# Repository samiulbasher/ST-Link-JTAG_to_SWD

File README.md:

# ST-Link JTAG to SWD Adapter

A simple, compact adapter that converts a legacy ARM 20-pin JTAG/SWD IDC connector to a standard SWD header. Compatible with ST-Link, J-Link, and other JTAG-based programmers.

---

## 🧰 General

This adapter is designed for developers to **simplify the development and debugging process**.

Instead of dealing with messy jumper wires or complex breakout boards, this provides a clean and reliable solution for converting JTAG to SWD—ideal for use with:

- ST-Link  
- J-Link  
- Other generic JTAG programmers

---

## 📌 Features

- **Plug & Play** — No need to look up datasheets or pinouts  
- **Developer-Friendly** — Saves time and reduces frustration  
- **Labeled Pins** — Clear labeling right on the PCB  
- **Reduces Errors** — Focus on your work, not wiring  
- **Compact** — Just 30x31 mm in size (*2-layer PCB*)

---

## 🧾 Applications

- Debugging and programming ARM Cortex-M microcontrollers  
- Quick SWD access for STM32 and other ARM-based chips  
- Works with any 20-pin JTAG header programmer

---

## 📷 Board Images

> Photos of the adapter and panelized PCB:

---

## 📍 Pin Details

All pin names are printed directly on the PCB.  
Here's a reference for the minimum required connections:

- **4 Pins** (1, 2, 3, 4) — Programming only  
- **6 Pins** (1, 2, 3, 4, 5, 6) — Full debugging + programming

---

## 🔌 Jumper Connection

When using different ST-Link versions:

- **Genuine ST-Link V2 or V3**:  
  Connect `VTarget (VTr)` to `VDD` [target's mcu `VDD`].

- **Clone ST-Link (usually ST-Link V2, e.g., Chinese versions)**:  
  Connect `3V3` to `VDD` [target's mcu `VDD`].

---

## 📦 Specifications

| Attribute           | Value                            |
|---------------------|----------------------------------|
| Dimensions           | 30 mm x 31 mm                   |
| Connector Type       | ARM 20-pin JTAG to SWD Header   |
| Programmer Support   | ST-Link, J-Link, and others     |

---

## ✅ Compatibility

| Programmer       | Compatible |
|------------------|------------|
| ST-Link V2       | ✅         |
| ST-Link V3       | ✅         |
| J-Link           | ✅         |
| Other JTAG headers | ✅       |

---

---

## 📁 Design Files & Gerber Files

- The `JTAG_to_SWD/` directory contains the original **KiCad project files**.  
  If you’d like to modify or customize the board, you can easily do so using KiCad.

- The `gerber/` directory includes **production-ready files** for PCB manufacturing.

  Inside it, you’ll find a `panel/V1.1/` subfolder — this contains the **panelized version** of the PCB (`JTAG_to_SWD_panel_V1.1.zip`).  
  This file is ready to upload directly to [JLCPCB](https://jlcpcb.com) for manufacturing.

💡 This is a **2-layer PCB**, and each panel contains **6 individual boards**.  
That means for just **$2**, you can get **30 PCBs** produced at JLCPCB!

---

## 📝 License

This project is released under the [MIT License](LICENSE).

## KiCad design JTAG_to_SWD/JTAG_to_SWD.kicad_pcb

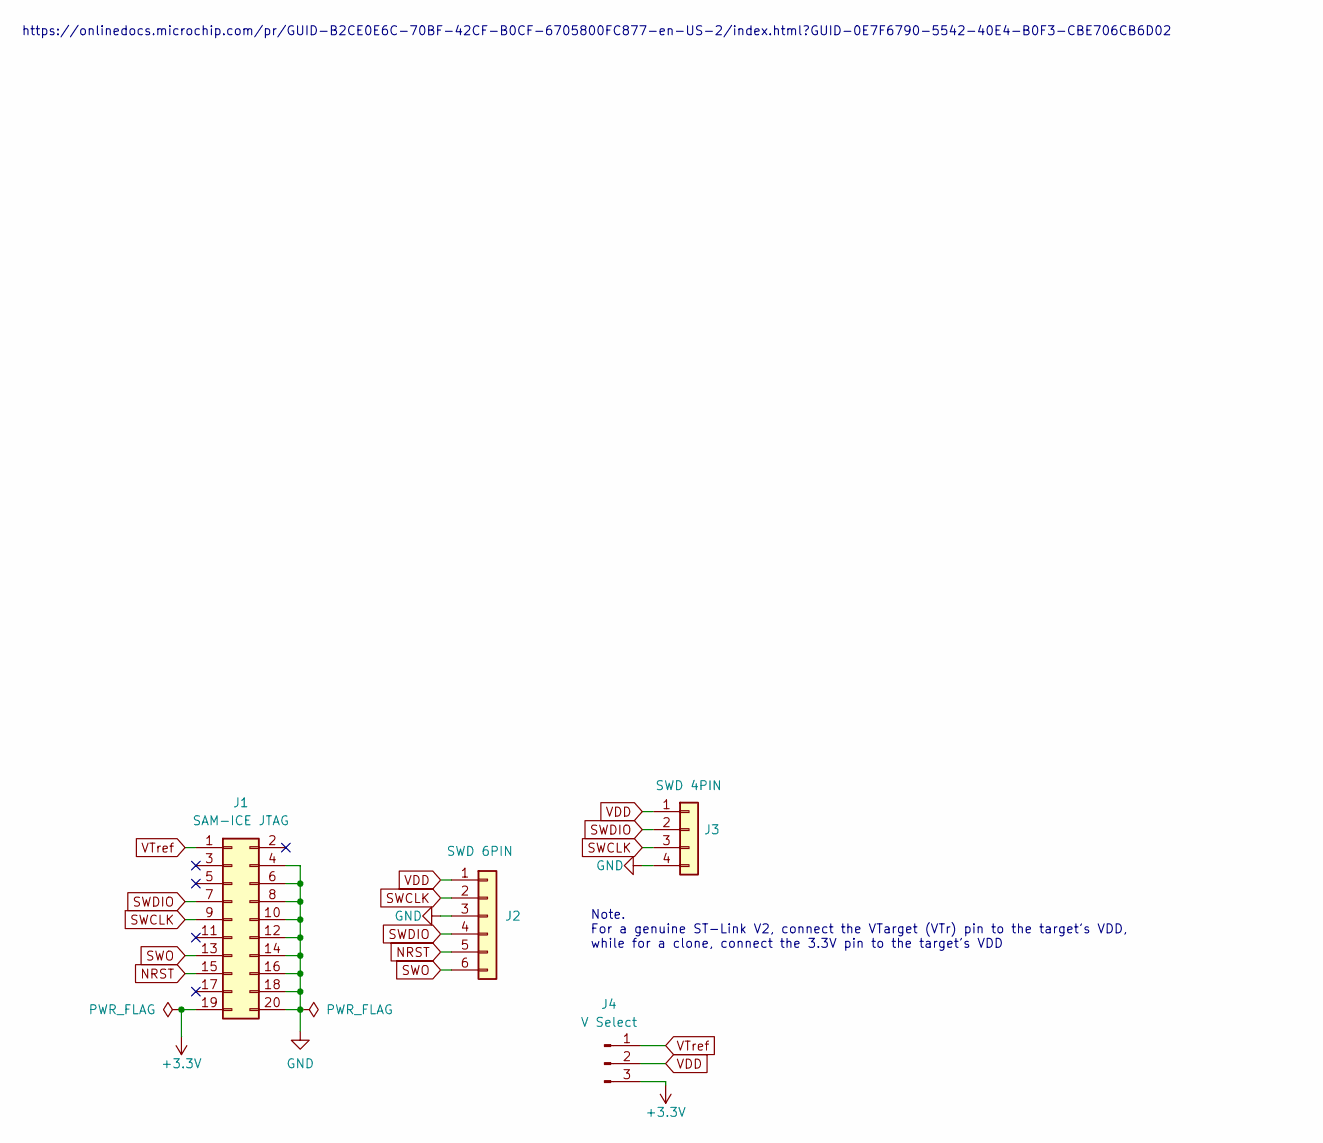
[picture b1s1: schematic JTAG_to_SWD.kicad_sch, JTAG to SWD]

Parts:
J1: SAM-ICE JTAG; PinSocket_2x10_P2.54mm_Vertical
J2: SWD 6PIN; PinHeader_1x06_P2.54mm_Vertical
J3: SWD 4PIN; PinHeader_1x04_P2.54mm_Vertical
J4: V Select; PinHeader_1x03_P2.54mm_Vertical

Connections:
+3.3V: J1.19, J4.3
GND: J1.4, J1.6, J1.8, J1.10, J1.12, J1.14, J1.16, J1.18, J1.20, J2.3, J3.4
NRST: J1.15, J2.5
SWCLK: J1.9, J2.2, J3.3
SWDIO: J1.7, J2.4, J3.2
SWO: J1.13, J2.6
VDD: J2.1, J3.1, J4.2
VTref: J1.1, J4.1

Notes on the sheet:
https://onlinedocs.microchip.com/pr/GUID-B2CE0E6C-70BF-42CF-B0CF-6705800FC877-en-US-2/index.html?GUID-0E7F6790-5542-40E4-B0F3-CBE706CB6D02
Note. For a genuine ST-Link V2, connect the VTarget (VTr) pin to the target's VDD, while for a clone, connect the 3.3V pin to the target's VDD

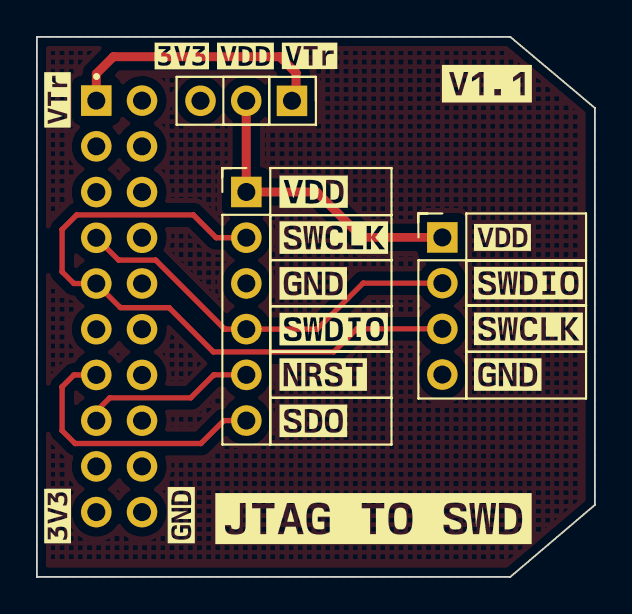
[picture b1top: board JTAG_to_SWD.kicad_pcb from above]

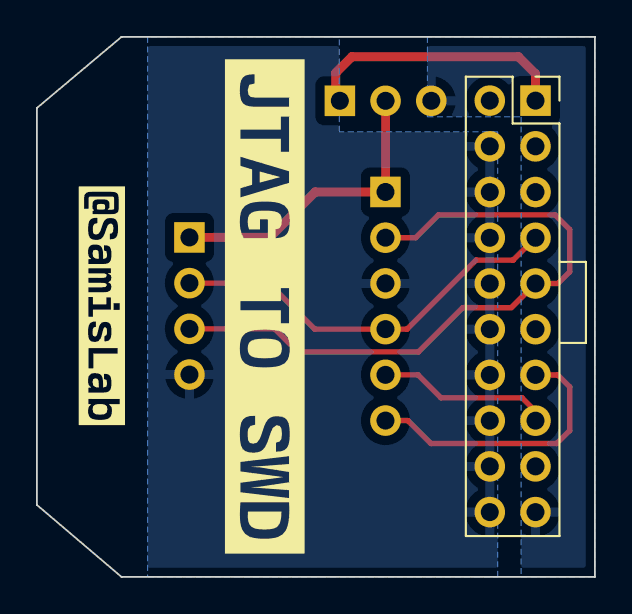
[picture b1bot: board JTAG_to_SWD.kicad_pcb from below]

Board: 2 copper layers, 31.0 x 30.0 mm, 24 parts (3 on the bottom side), 8 nets.

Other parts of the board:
kibuzzard-652CA4AC: G***; kibuzzard-652CA4AC
kibuzzard-652CAEF1, kibuzzard-652CAEF1#2: G***; kibuzzard-652CAEF1
kibuzzard-652CCC4E: G***; kibuzzard-652CCC4E
kibuzzard-6539E1A4, kibuzzard-6539E1A4#2: G***; kibuzzard-6539E1A4
kibuzzard-6539E4EE: G***; kibuzzard-6539E4EE
kibuzzard-6539E7D0: G***; kibuzzard-6539E7D0
kibuzzard-6539E8AF: G***; kibuzzard-6539E8AF
kibuzzard-6539E8D8: G***; kibuzzard-6539E8D8
kibuzzard-6539E58F: G***; kibuzzard-6539E58F
kibuzzard-6539E59E: G***; kibuzzard-6539E59E
kibuzzard-6539E162: G***; kibuzzard-6539E162
kibuzzard-6539E581: G***; kibuzzard-6539E581
kibuzzard-6539E611: G***; kibuzzard-6539E611
kibuzzard-6539E616: G***; kibuzzard-6539E616
kibuzzard-6539E628: G***; kibuzzard-6539E628
kibuzzard-6539E918: G***; kibuzzard-6539E918
kibuzzard-6539E952: G***; kibuzzard-6539E952
kibuzzard-6656AA27: G***; kibuzzard-6656AA27
